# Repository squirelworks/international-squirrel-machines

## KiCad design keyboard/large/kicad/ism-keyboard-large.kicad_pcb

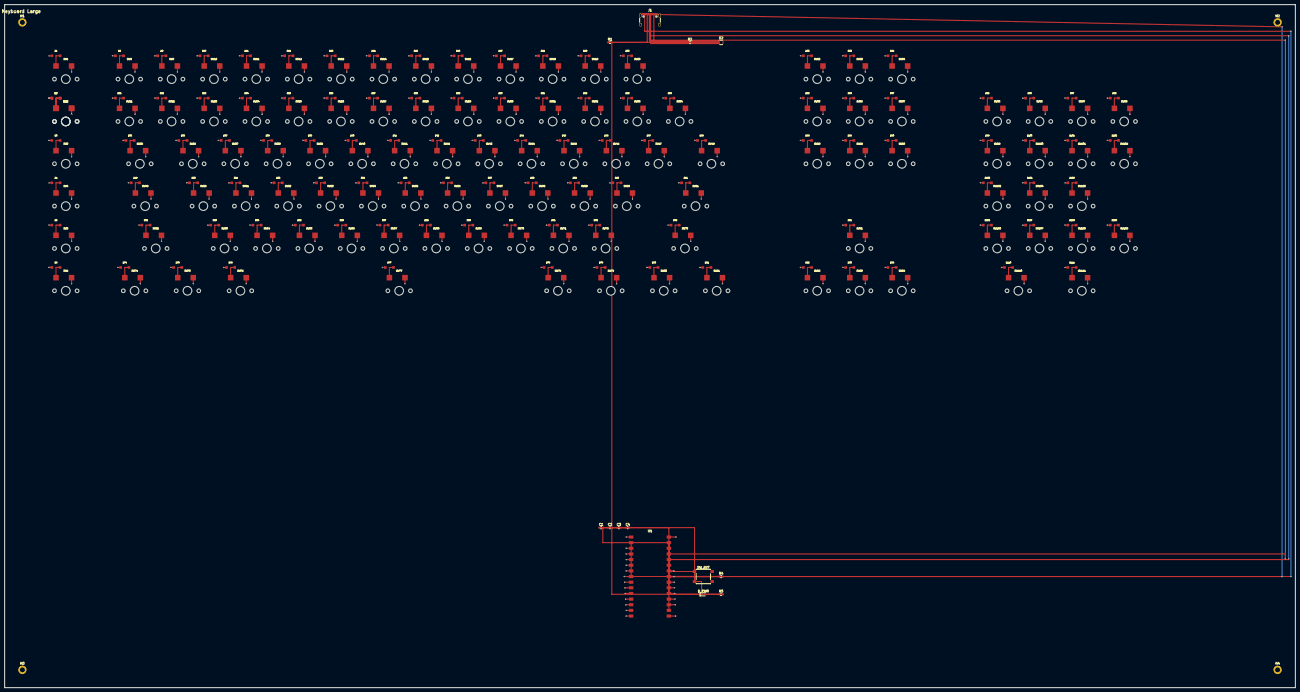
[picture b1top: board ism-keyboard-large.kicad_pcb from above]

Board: 4 copper layers, 580.8 x 307.4 mm, 239 parts (0 on the bottom side), 143 nets.

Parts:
C1, C2, C3, C4: 100nF; C_0603_1608Metric
D1, D2, D3, D4, D5, D6, D7, D8, D9, D10, D11, D12, D13, D14, D15, D16, D17, D18, D19, D20, D21, D22, D23, D24, D25, D26, D27, D28, D29, D30, D31, D32, D33, D34, D35, D36, D37, D38, D39, D40, D41, D42, D43, D44, D45, D46, D47, D48, D49, D50, D51, D52, D53, D54, D55, D56, D57, D58, D59, D60, D61, D62, D63, D64, D65, D66, D67, D68, D69, D70, D71, D72, D73, D74, D75, D76, D77, D78, D79, D80, D81, D82, D83, D84, D85, D86, D87, D88, D89, D90, D91, D92, D93, D94, D95, D96, D97, D98, D99, D100, D101, D102, D103, D104, D105, D106, D107, D108, D109, D110, D111: 1N4148W; D_SOD123_nocrt
D_PWR: LED; LED_0603_1608Metric
H1, H2, H3, H4: M2; MountingHole_2.2mm_M2_DIN965_Pad
J1: USB_C; USB_C_Receptacle_GCT_USB4105-xx-A_16P_TopMnt_Horizontal
R1, R2: 5.1k; R_0603_1608Metric
R4: 10k; R_0603_1608Metric
R5: 1k; R_0603_1608Metric
SW1: M1; SW_MX_Hotswap
SW2: M2; SW_MX_Hotswap
SW3: M3; SW_MX_Hotswap
SW4: M4; SW_MX_Hotswap
SW5: M5; SW_MX_Hotswap
SW6: M6; SW_MX_Hotswap
SW7: M7; SW_MX_Hotswap
SW8: ESC; SW_MX_Hotswap
SW9: F1; SW_MX_Hotswap
SW10: F2; SW_MX_Hotswap
SW11: F3; SW_MX_Hotswap
SW12: F4; SW_MX_Hotswap
SW13: F5; SW_MX_Hotswap
SW14: F6; SW_MX_Hotswap
SW15: F7; SW_MX_Hotswap
SW16: F8; SW_MX_Hotswap
SW17: F9; SW_MX_Hotswap
SW18: F10; SW_MX_Hotswap
SW19: F11; SW_MX_Hotswap
SW20: F12; SW_MX_Hotswap
SW21: GRV; SW_MX_Hotswap
SW22: 1; SW_MX_Hotswap
SW23: 2; SW_MX_Hotswap
SW24: 3; SW_MX_Hotswap
SW25: 4; SW_MX_Hotswap
SW26: 5; SW_MX_Hotswap
SW27: 6; SW_MX_Hotswap
SW28: 7; SW_MX_Hotswap
SW29: 8; SW_MX_Hotswap
SW30: 9; SW_MX_Hotswap
SW31: 0; SW_MX_Hotswap
SW32: MIN; SW_MX_Hotswap
SW33: EQL; SW_MX_Hotswap
SW34: BSPC; SW_MX_Hotswap
SW35: TAB; SW_MX_Hotswap
SW36: Q; SW_MX_Hotswap
SW37: W; SW_MX_Hotswap
SW38: E; SW_MX_Hotswap
SW39: R; SW_MX_Hotswap
SW40: T; SW_MX_Hotswap
SW41: Y; SW_MX_Hotswap
SW42: U; SW_MX_Hotswap
SW43: I; SW_MX_Hotswap
SW44: O; SW_MX_Hotswap
SW45: P; SW_MX_Hotswap
SW46: LBRC; SW_MX_Hotswap
SW47: RBRC; SW_MX_Hotswap
SW48: BSLS; SW_MX_Hotswap
SW49: CAPS; SW_MX_Hotswap
SW50: A; SW_MX_Hotswap
SW51: S; SW_MX_Hotswap
SW52: D; SW_MX_Hotswap
SW53: F; SW_MX_Hotswap
SW54: G; SW_MX_Hotswap
SW55: H; SW_MX_Hotswap
SW56: J; SW_MX_Hotswap
SW57: K; SW_MX_Hotswap
SW58: L; SW_MX_Hotswap
SW59: SCLN; SW_MX_Hotswap
SW60: QUOT; SW_MX_Hotswap
SW61: ENT; SW_MX_Hotswap
SW62: LSFT; SW_MX_Hotswap
SW63: Z; SW_MX_Hotswap
SW64: X; SW_MX_Hotswap
SW65: C; SW_MX_Hotswap
SW66: V; SW_MX_Hotswap
SW67: B; SW_MX_Hotswap
SW68: N; SW_MX_Hotswap
SW69: M; SW_MX_Hotswap
SW70: COMM; SW_MX_Hotswap
SW71: DOT; SW_MX_Hotswap
SW72: SLSH; SW_MX_Hotswap
SW73: RSFT; SW_MX_Hotswap
SW74: LCTL; SW_MX_Hotswap
SW75: LGUI; SW_MX_Hotswap
SW76: LALT; SW_MX_Hotswap
SW77: SPC; SW_MX_Hotswap
SW78: RALT; SW_MX_Hotswap
SW79: RGUI; SW_MX_Hotswap
SW80: MENU; SW_MX_Hotswap
SW81: RCTL; SW_MX_Hotswap
SW82: PRSC; SW_MX_Hotswap
SW83: SLCK; SW_MX_Hotswap
SW84: PAUSE; SW_MX_Hotswap
SW85: INS; SW_MX_Hotswap
SW86: HOME; SW_MX_Hotswap
SW87: PGUP; SW_MX_Hotswap
SW88: DEL; SW_MX_Hotswap
SW89: END; SW_MX_Hotswap
SW90: PGDN; SW_MX_Hotswap
SW91: UP; SW_MX_Hotswap
SW92: LEFT; SW_MX_Hotswap
SW93: DOWN; SW_MX_Hotswap
SW94: RIGHT; SW_MX_Hotswap
SW95: NUMLK; SW_MX_Hotswap
SW96: NPDIV; SW_MX_Hotswap
SW97: NPMUL; SW_MX_Hotswap
SW98: NPSUB; SW_MX_Hotswap
SW99: NP7; SW_MX_Hotswap
SW100: NP8; SW_MX_Hotswap
SW101: NP9; SW_MX_Hotswap
SW102: NPADD; SW_MX_Hotswap
SW103: NP4; SW_MX_Hotswap
SW104: NP5; SW_MX_Hotswap
SW105: NP6; SW_MX_Hotswap
SW106: NP1; SW_MX_Hotswap
SW107: NP2; SW_MX_Hotswap
SW108: NP3; SW_MX_Hotswap
SW109: NPENT; SW_MX_Hotswap
SW110: NP0; SW_MX_Hotswap
SW111: NPDOT; SW_MX_Hotswap
SW_RST: RESET; SW_SPST_PTS645
U1: RP2040_MOD; ISM_RP2040_Module
U2: USBLC6-2SC6; SOT-666

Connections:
+3V3: C1.1, C2.1, C3.1, C4.1, R4.2, R5.1, U1.14
+5V: J1.A4, J1.A9, J1.B4, J1.B9, U1.15, U2.5
CC1: J1.A5, R1.1
CC2: J1.B5, R2.1
COL0: D8.1, D21.1, D35.1, D49.1, D62.1, D74.1, D95.1, U1.7
COL1: D9.1, D22.1, D36.1, D50.1, D63.1, D75.1, D96.1, U1.8
COL2: D10.1, D23.1, D37.1, D51.1, D64.1, D76.1, D97.1, U1.9
COL3: D11.1, D24.1, D38.1, D52.1, D65.1, D77.1, D98.1, U1.10
COL4: D12.1, D25.1, D39.1, D53.1, D66.1, D78.1, D99.1, U1.11
COL5: D13.1, D26.1, D40.1, D54.1, D67.1, D79.1, D100.1, U1.12
COL6: D14.1, D27.1, D41.1, D55.1, D68.1, D80.1, D101.1, U1.13
COL7: D15.1, D28.1, D42.1, D56.1, D69.1, D81.1, D102.1, U1.19
COL8: D16.1, D29.1, D43.1, D57.1, D70.1, D84.1, D103.1, U1.20
COL9: D17.1, D30.1, D44.1, D58.1, D71.1, D92.1, D104.1, U1.21
COL10: D18.1, D31.1, D45.1, D59.1, D72.1, D93.1, D105.1, U1.22
COL11: D19.1, D32.1, D46.1, D60.1, D73.1, D94.1, D106.1, U1.23
COL12: D20.1, D33.1, D47.1, D61.1, D89.1, D107.1, D110.1, U1.24
COL13: D34.1, D48.1, D82.1, D86.1, D90.1, D108.1, D111.1, U1.25
COL14: D83.1, D85.1, D87.1, D88.1, D91.1, D109.1, U1.28
COL15: D1.1, D2.1, D3.1, D4.1, D5.1, D6.1, D7.1, U1.30
GND: C1.2, C2.2, C3.2, C4.2, D_PWR.1, J1.A1, J1.A8, J1.A12, J1.B1, J1.B8, J1.B12, J1.S1, R1.2, R2.2, SW_RST.2, U1.1, U1.26, U2.2
LED_A: D_PWR.2, R5.2
NET_SW1: D1.2, SW1.2
NET_SW2: D2.2, SW2.2
NET_SW3: D3.2, SW3.2
NET_SW4: D4.2, SW4.2
NET_SW5: D5.2, SW5.2
NET_SW6: D6.2, SW6.2
NET_SW7: D7.2, SW7.2
NET_SW8: D8.2, SW8.2
NET_SW9: D9.2, SW9.2
NET_SW10: D10.2, SW10.2
NET_SW11: D11.2, SW11.2
NET_SW12: D12.2, SW12.2
NET_SW13: D13.2, SW13.2
NET_SW14: D14.2, SW14.2
NET_SW15: D15.2, SW15.2
NET_SW16: D16.2, SW16.2
NET_SW17: D17.2, SW17.2
NET_SW18: D18.2, SW18.2
NET_SW19: D19.2, SW19.2
NET_SW20: D20.2, SW20.2
NET_SW21: D21.2, SW21.2
NET_SW22: D22.2, SW22.2
NET_SW23: D23.2, SW23.2
NET_SW24: D24.2, SW24.2
NET_SW25: D25.2, SW25.2
NET_SW26: D26.2, SW26.2
NET_SW27: D27.2, SW27.2
NET_SW28: D28.2, SW28.2
NET_SW29: D29.2, SW29.2
NET_SW30: D30.2, SW30.2
NET_SW31: D31.2, SW31.2
NET_SW32: D32.2, SW32.2
NET_SW33: D33.2, SW33.2
NET_SW34: D34.2, SW34.2
NET_SW35: D35.2, SW35.2
NET_SW36: D36.2, SW36.2
NET_SW37: D37.2, SW37.2
NET_SW38: D38.2, SW38.2
NET_SW39: D39.2, SW39.2
NET_SW40: D40.2, SW40.2
NET_SW41: D41.2, SW41.2
NET_SW42: D42.2, SW42.2
NET_SW43: D43.2, SW43.2
NET_SW44: D44.2, SW44.2
NET_SW45: D45.2, SW45.2
NET_SW46: D46.2, SW46.2
NET_SW47: D47.2, SW47.2
NET_SW48: D48.2, SW48.2
NET_SW49: D49.2, SW49.2
NET_SW50: D50.2, SW50.2
NET_SW51: D51.2, SW51.2
NET_SW52: D52.2, SW52.2
NET_SW53: D53.2, SW53.2
NET_SW54: D54.2, SW54.2
NET_SW55: D55.2, SW55.2
NET_SW56: D56.2, SW56.2
NET_SW57: D57.2, SW57.2
NET_SW58: D58.2, SW58.2
NET_SW59: D59.2, SW59.2
NET_SW60: D60.2, SW60.2
NET_SW61: D61.2, SW61.2
NET_SW62: D62.2, SW62.2
NET_SW63: D63.2, SW63.2
NET_SW64: D64.2, SW64.2
NET_SW65: D65.2, SW65.2
NET_SW66: D66.2, SW66.2
NET_SW67: D67.2, SW67.2
NET_SW68: D68.2, SW68.2
NET_SW69: D69.2, SW69.2
NET_SW70: D70.2, SW70.2
NET_SW71: D71.2, SW71.2
NET_SW72: D72.2, SW72.2
NET_SW73: D73.2, SW73.2
NET_SW74: D74.2, SW74.2
NET_SW75: D75.2, SW75.2
NET_SW76: D76.2, SW76.2
NET_SW77: D77.2, SW77.2
NET_SW78: D78.2, SW78.2
NET_SW79: D79.2, SW79.2
NET_SW80: D80.2, SW80.2
NET_SW81: D81.2, SW81.2
NET_SW82: D82.2, SW82.2
NET_SW83: D83.2, SW83.2
NET_SW84: D84.2, SW84.2
NET_SW85: D85.2, SW85.2
NET_SW86: D86.2, SW86.2
NET_SW87: D87.2, SW87.2
NET_SW88: D88.2, SW88.2
NET_SW89: D89.2, SW89.2
NET_SW90: D90.2, SW90.2
NET_SW91: D91.2, SW91.2
NET_SW92: D92.2, SW92.2
NET_SW93: D93.2, SW93.2
NET_SW94: D94.2, SW94.2
NET_SW95: D95.2, SW95.2
NET_SW96: D96.2, SW96.2
NET_SW97: D97.2, SW97.2
NET_SW98: D98.2, SW98.2
NET_SW99: D99.2, SW99.2
NET_SW100: D100.2, SW100.2
NET_SW101: D101.2, SW101.2
NET_SW102: D102.2, SW102.2
NET_SW103: D103.2, SW103.2
NET_SW104: D104.2, SW104.2
NET_SW105: D105.2, SW105.2
NET_SW106: D106.2, SW106.2
NET_SW107: D107.2, SW107.2
NET_SW108: D108.2, SW108.2
NET_SW109: D109.2, SW109.2
NET_SW110: D110.2, SW110.2
NET_SW111: D111.2, SW111.2
ROW0: SW1.1, SW8.1, SW9.1, SW10.1, SW11.1, SW12.1, SW13.1, SW14.1, SW15.1, SW16.1, SW17.1, SW18.1, SW19.1, SW20.1, SW82.1, SW83.1, U1.2
ROW1: SW2.1, SW21.1, SW22.1, SW23.1, SW24.1, SW25.1, SW26.1, SW27.1, SW28.1, SW29.1, SW30.1, SW31.1, SW32.1, SW33.1, SW34.1, SW85.1, U1.3
ROW2: SW3.1, SW35.1, SW36.1, SW37.1, SW38.1, SW39.1, SW40.1, SW41.1, SW42.1, SW43.1, SW44.1, SW45.1, SW46.1, SW47.1, SW48.1, SW88.1, U1.4
ROW3: SW4.1, SW49.1, SW50.1, SW51.1, SW52.1, SW53.1, SW54.1, SW55.1, SW56.1, SW57.1, SW58.1, SW59.1, SW60.1, SW61.1, SW86.1, SW87.1, U1.5
ROW4: SW5.1, SW62.1, SW63.1, SW64.1, SW65.1, SW66.1, SW67.1, SW68.1, SW69.1, SW70.1, SW71.1, SW72.1, SW73.1, SW89.1, SW90.1, SW91.1, U1.6
ROW5: SW6.1, SW74.1, SW75.1, SW76.1, SW77.1, SW78.1, SW79.1, SW80.1, SW81.1, SW84.1, SW92.1, SW93.1, SW94.1, SW110.1, SW111.1, U1.27
ROW6: SW7.1, SW95.1, SW96.1, SW97.1, SW98.1, SW99.1, SW100.1, SW101.1, SW102.1, SW103.1, SW104.1, SW105.1, SW106.1, SW107.1, SW108.1, SW109.1, U1.29
RUN: R4.1, SW_RST.1, U1.18
USB_DM: J1.A7, J1.B7, U1.16, U2.3, U2.4
USB_DP: J1.A6, J1.B6, U1.17, U2.1, U2.6

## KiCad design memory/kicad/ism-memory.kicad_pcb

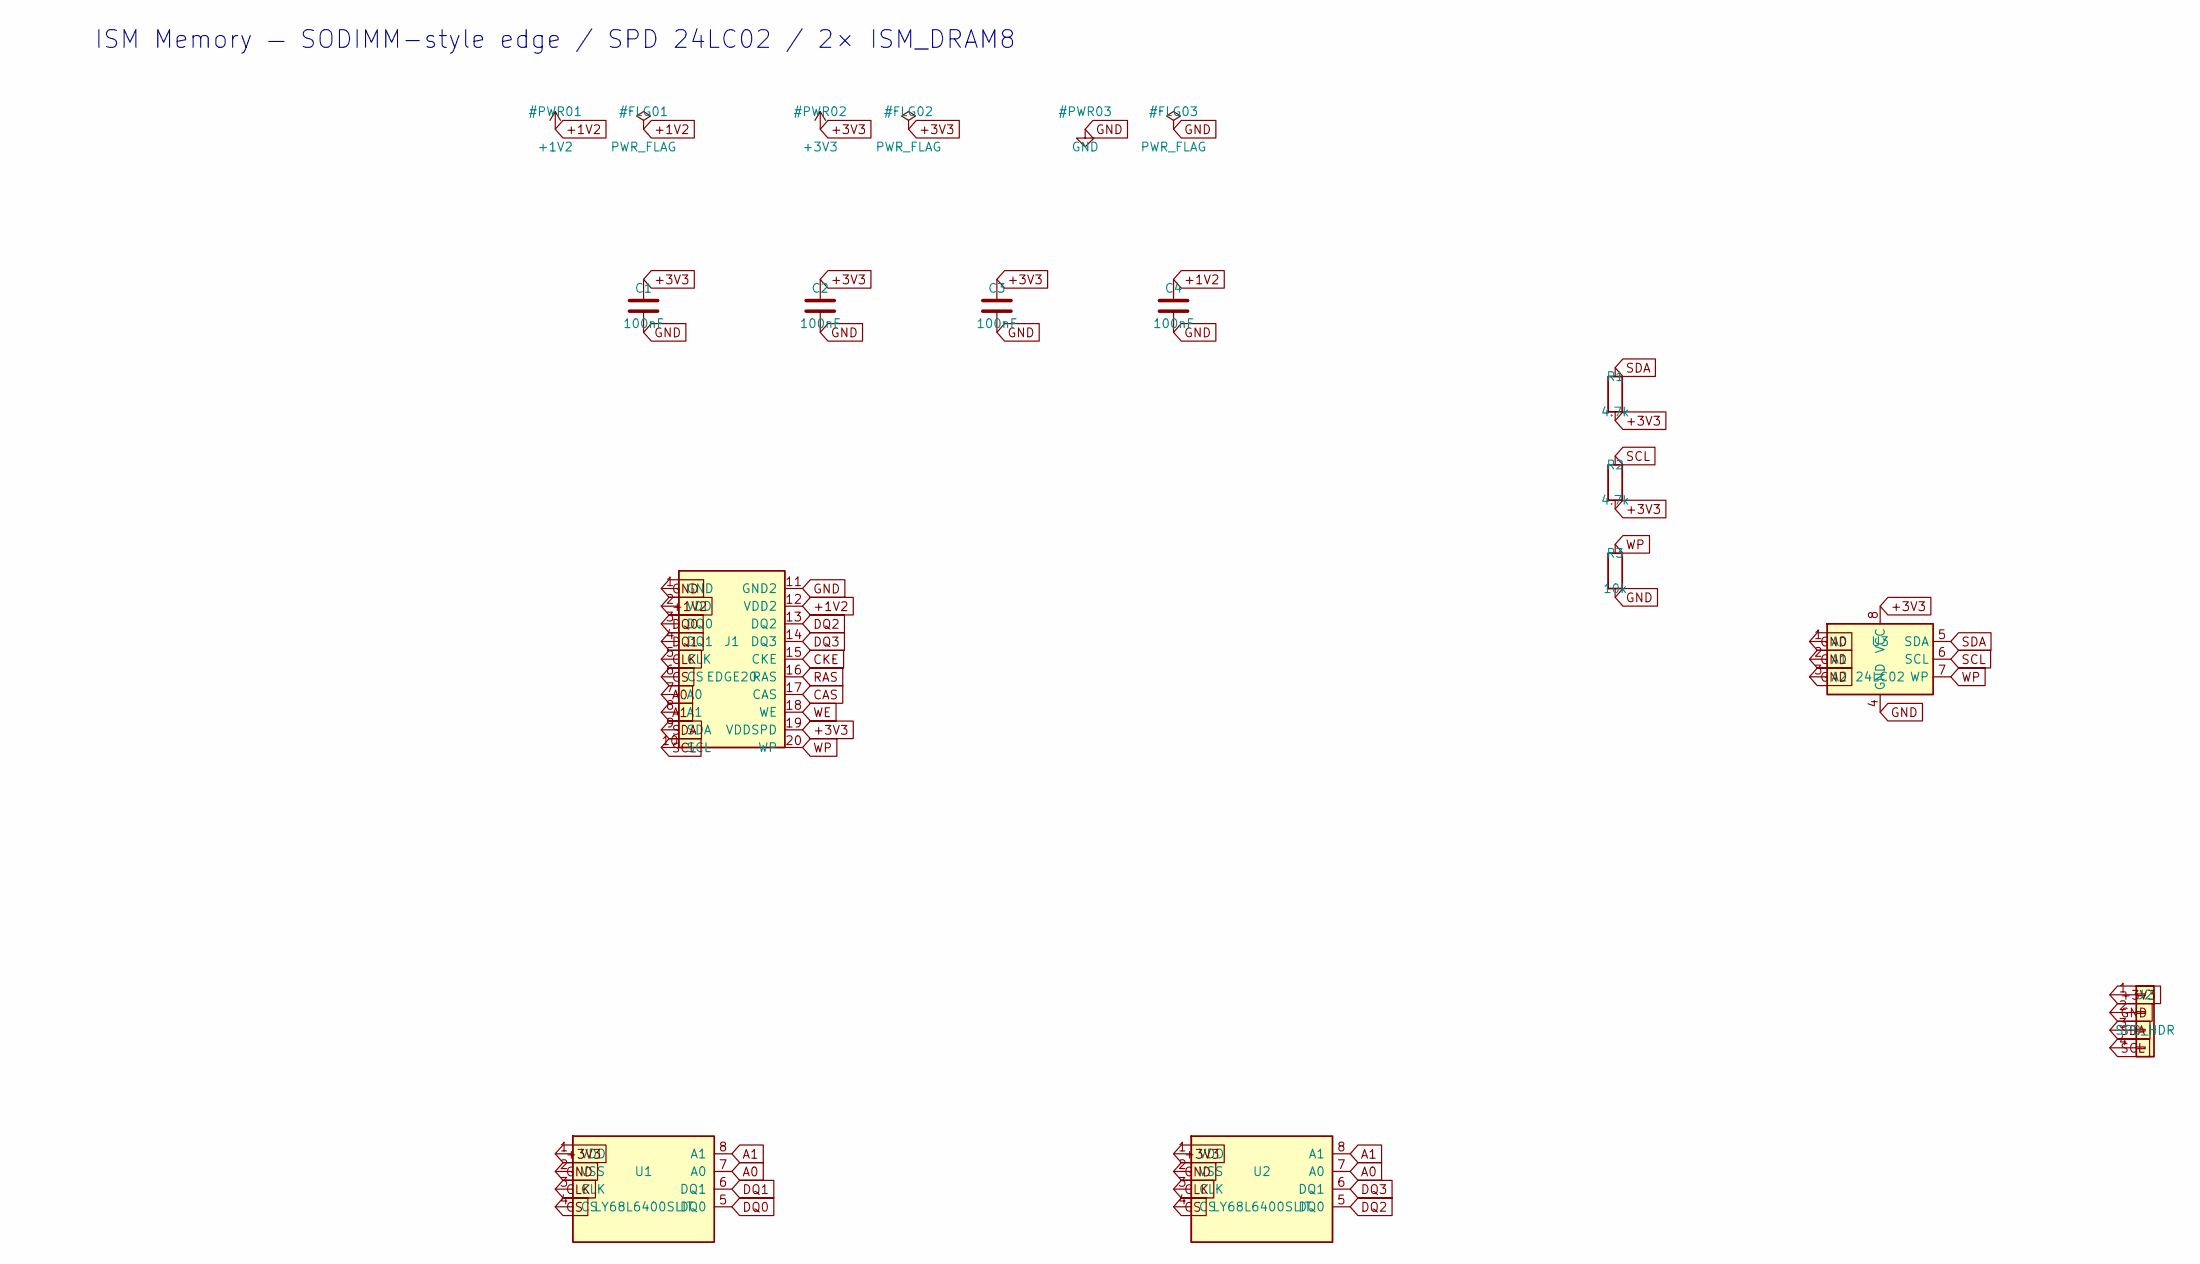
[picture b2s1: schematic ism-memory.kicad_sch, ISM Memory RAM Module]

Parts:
C1, C2, C3, C4: 100nF; C_0603_1608Metric; LCSC C14663
J1: EDGE20; ISM_SO_DIMM_Edge20
J2: SPD_HDR; PinHeader_1x04_P2.54mm_Vertical
R1, R2: 4.7k; R_0603_1608Metric; LCSC C23141
R3: 10k; R_0603_1608Metric; LCSC C25804
U1, U2: LY68L6400SLIT; SOIC-8_3.9x4.9mm_P1.27mm; MPN LY68L6400SLIT; LCSC C261881
U3: 24LC02; SOIC-8_3.9x4.9mm_P1.27mm; MPN 24LC02B; LCSC C7500

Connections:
+1V2: C4.1, J1.2 (VDD), J1.12 (VDD2)
+3V3: C1.1, C2.1, C3.1, J1.19 (VDDSPD), J2.1, R1.2, R2.2, U1.1 (VDD), U2.1 (VDD), U3.8 (VCC)
A0: J1.7 (A0), U1.7 (A0), U2.7 (A0)
A1: J1.8 (A1), U1.8 (A1), U2.8 (A1)
CAS: J1.17 (CAS)
CKE: J1.15 (CKE)
CLK: J1.5 (CLK), U1.3 (CLK), U2.3 (CLK)
CS: J1.6 (CS), U1.4 (CS), U2.4 (CS)
DQ0: J1.3 (DQ0), U1.5 (DQ0)
DQ1: J1.4 (DQ1), U1.6 (DQ1)
DQ2: J1.13 (DQ2), U2.5 (DQ0)
DQ3: J1.14 (DQ3), U2.6 (DQ1)
GND: C1.2, C2.2, C3.2, C4.2, J1.1 (GND), J1.11 (GND2), J2.2, R3.2, U1.2 (VSS), U2.2 (VSS), U3.1 (A0), U3.2 (A1), U3.3 (A2), U3.4 (GND)
RAS: J1.16 (RAS)
SCL: J1.10 (SCL), J2.4, R2.1, U3.6 (SCL)
SDA: J1.9 (SDA), J2.3, R1.1, U3.5 (SDA)
WE: J1.18 (WE)
WP: J1.20 (WP), R3.1, U3.7 (WP)

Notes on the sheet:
ISM Memory — SODIMM-style edge / SPD 24LC02 / 2× ISM_DRAM8

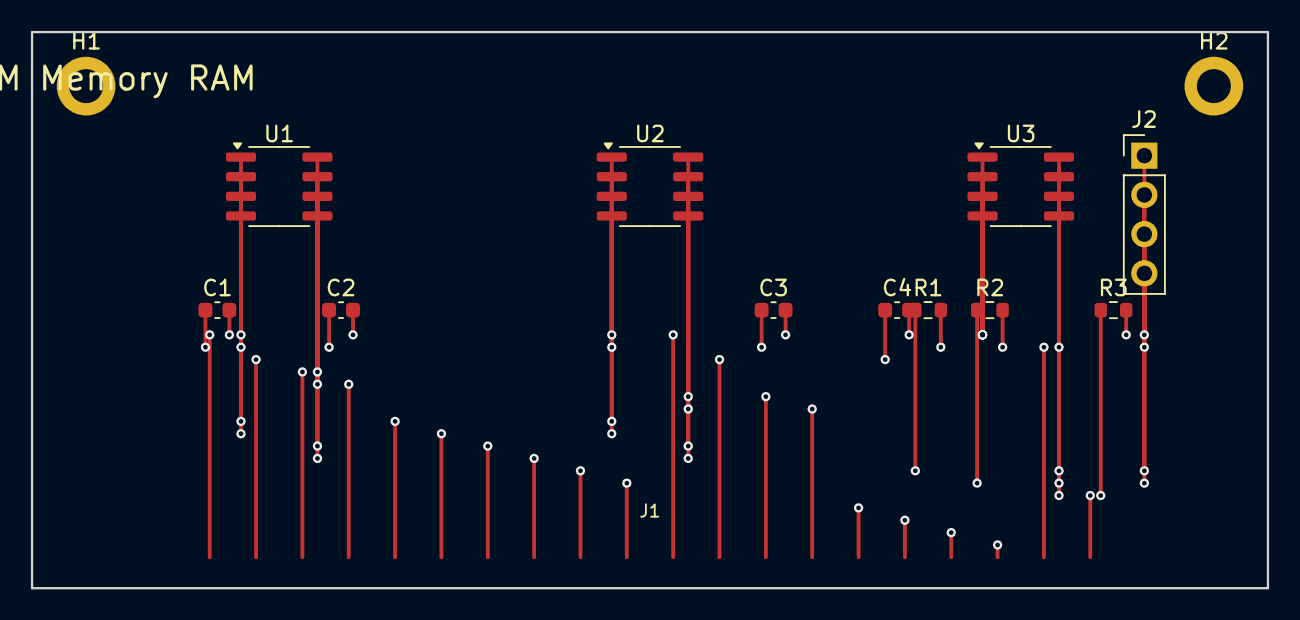
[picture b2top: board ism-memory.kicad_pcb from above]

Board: 4 copper layers, 80.0 x 36.0 mm, 14 parts (0 on the bottom side), 14 nets.

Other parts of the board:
H1, H2: M2; MountingHole_2.2mm_M2_DIN965_Pad

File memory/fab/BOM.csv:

Designator,Value,Footprint,Quantity,Manufacturer,MPN,LCSC,Notes
"U1,U2",LY68L6400SLIT,SOIC-8_3.9x4.9mm,2,Lyontek,LY68L6400SLIT,C261881,Default SMT pop — 64 Mbit SPI/QPI PSRAM. Optional alt land: ISM:ISM_DRAM_SOIC
U3,24LC02,SOIC-8,1,Microchip,24LC02B,C7500,SPD EEPROM
J1,EDGE20,ISM_SO_DIMM_Edge20,1,ISM,ISM-EDGE20,,No LCSC — edge fingers (PCB feature)
J2,1x04,PinHeader 2.54,1,,HDR-1x4,C124423,SPD test header
"R1,R2",4.7k,0603,2,,4.7k,C23141,I2C pull-up
R3,10k,0603,1,,10k,C25804,WP pull-down
C1-C4,100nF,0603,4,,100nF,C14663,
"H1,H2",M2,MountingHole,2,,,,No LCSC — mechanical NPTH

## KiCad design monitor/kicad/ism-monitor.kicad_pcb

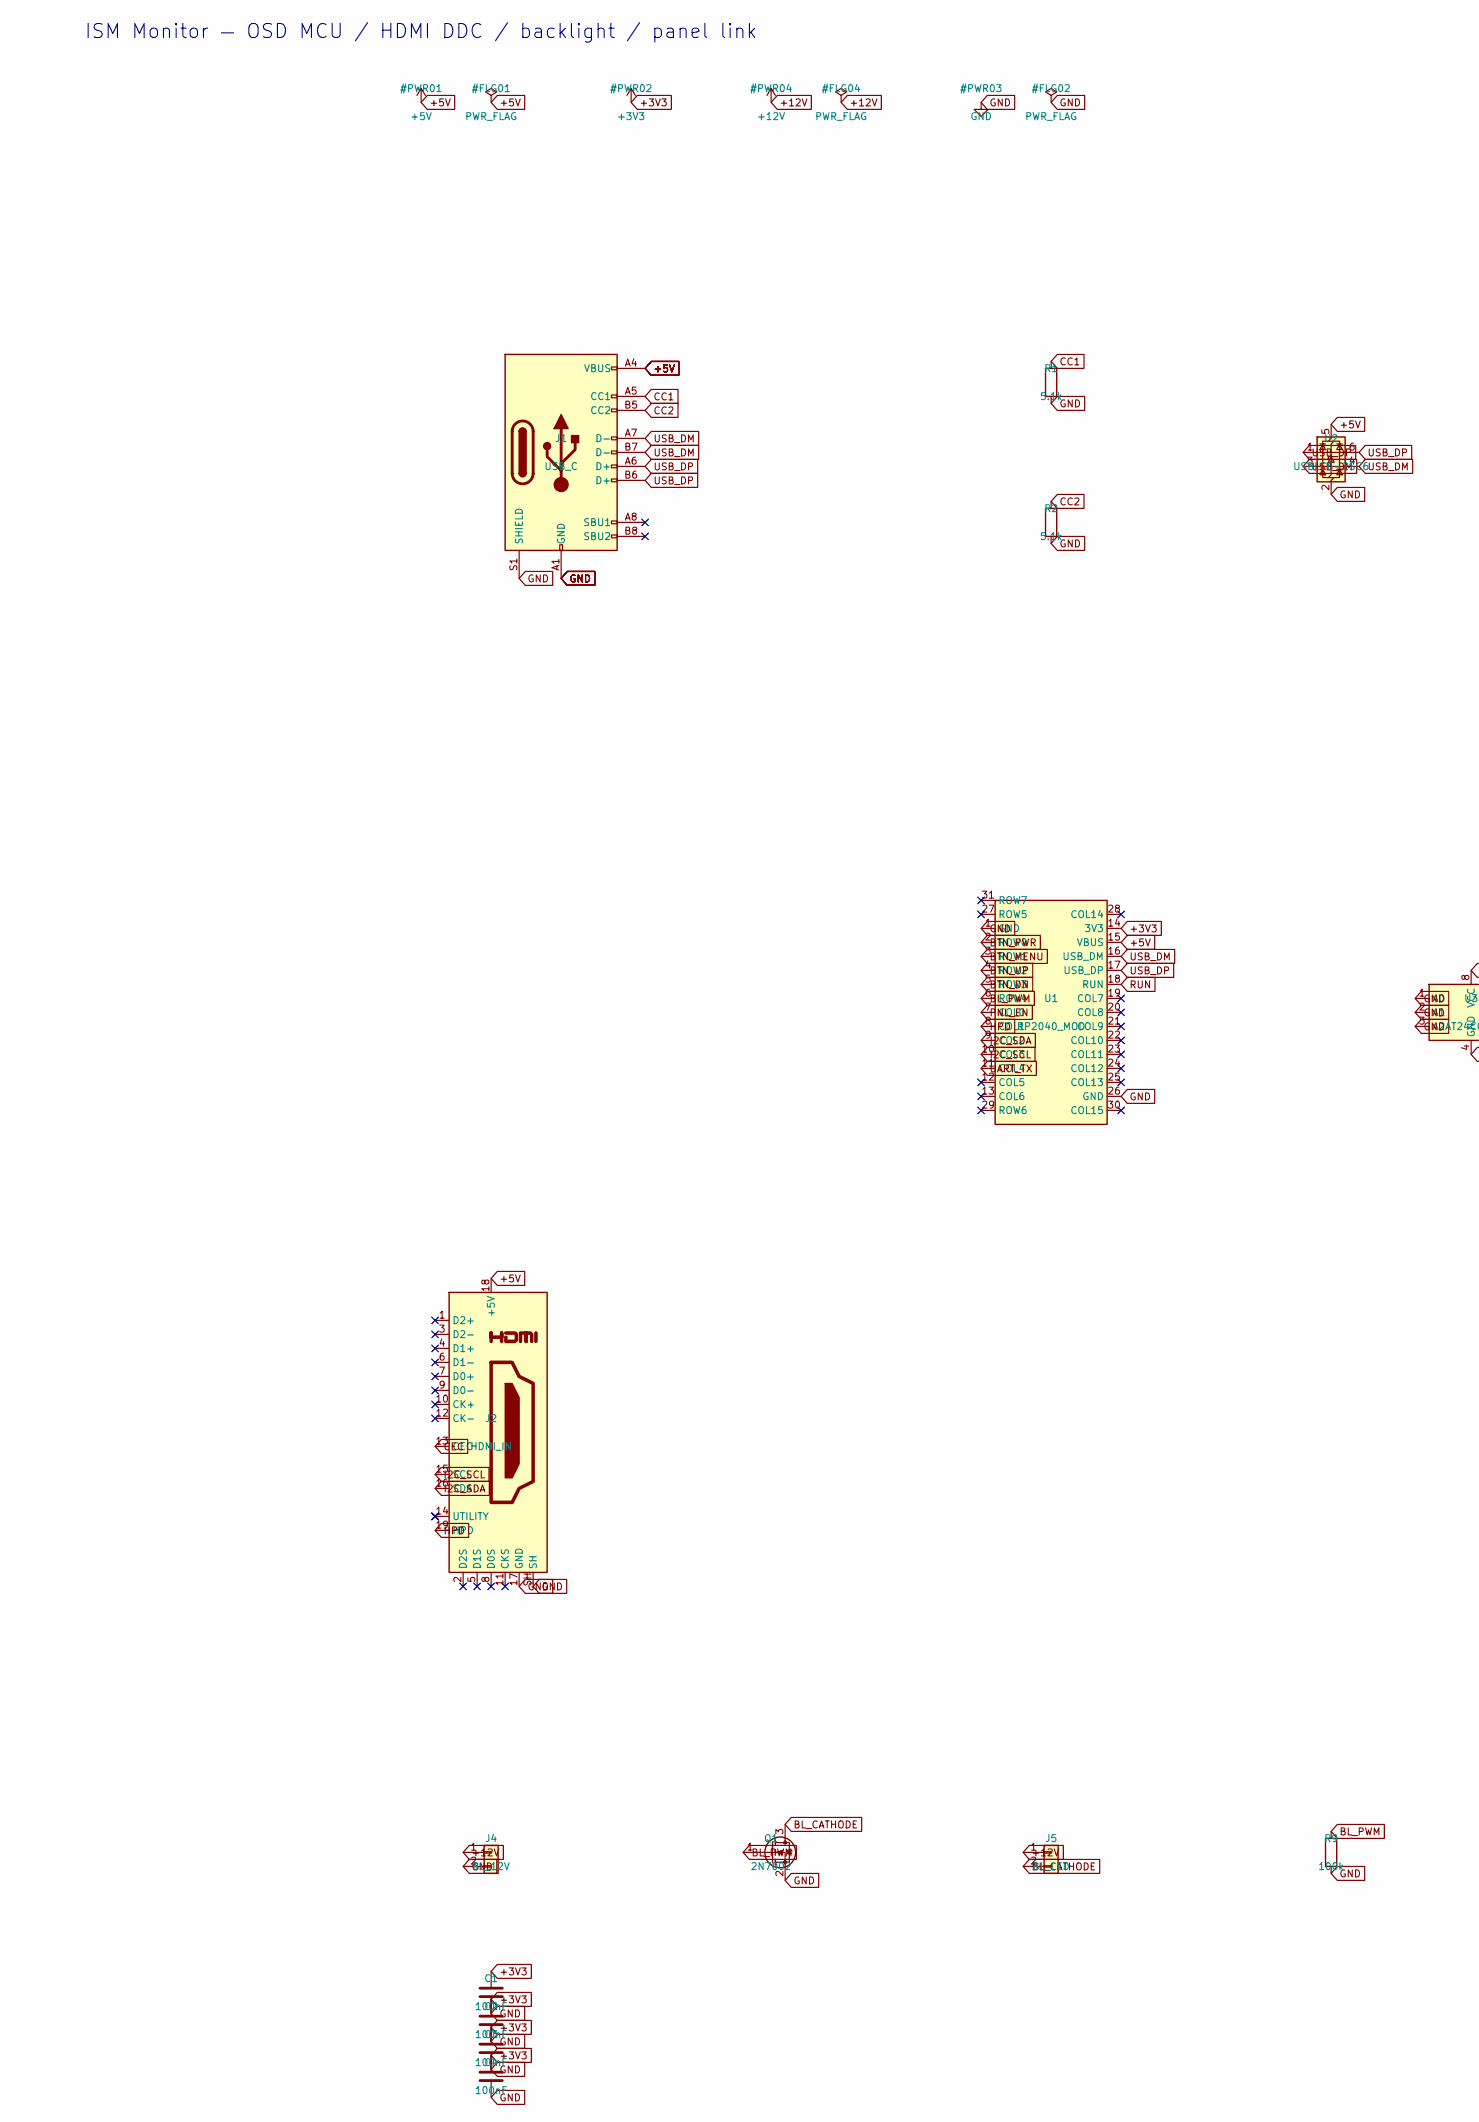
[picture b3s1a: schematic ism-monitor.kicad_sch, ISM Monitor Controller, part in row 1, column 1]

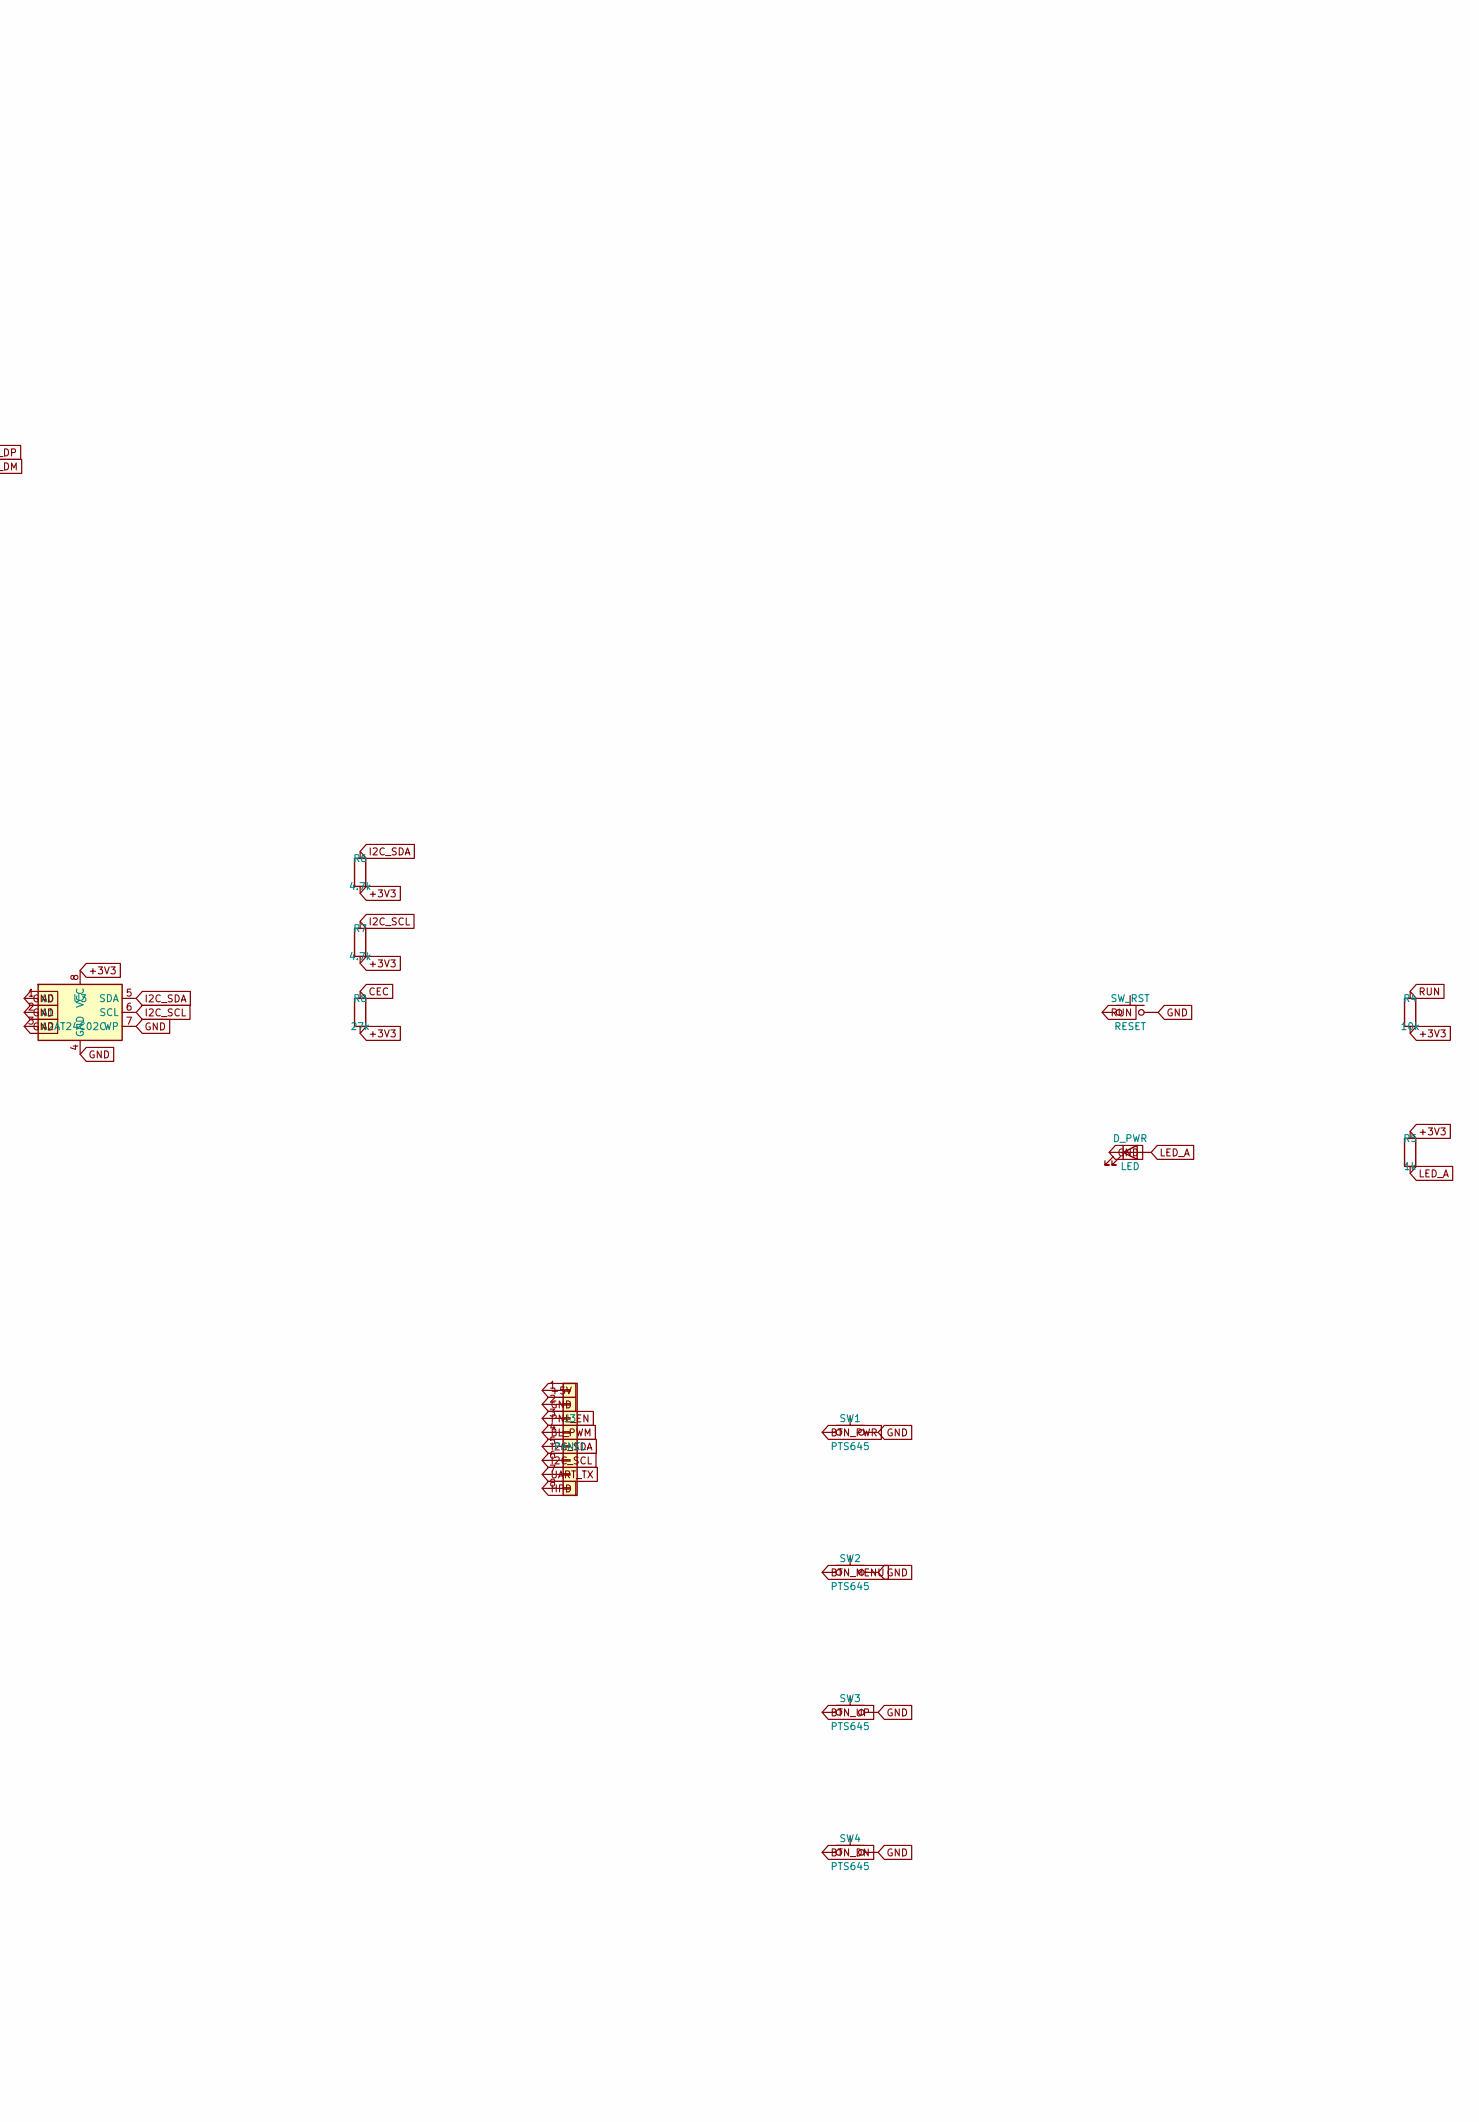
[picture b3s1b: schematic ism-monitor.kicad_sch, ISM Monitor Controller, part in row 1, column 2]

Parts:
C1, C2, C3, C4: 100nF; C_0603_1608Metric; LCSC C14663
D_PWR: LED; LED_0603_1608Metric; LCSC C2286
J1: USB_C; USB_C_Receptacle_GCT_USB4105-xx-A_16P_TopMnt_Horizontal; LCSC C165948
J2: HDMI_IN; HDMI_A_Amphenol_10029449-x01xLF_Horizontal; LCSC C132555
J3: PANEL; PinHeader_1x08_P2.54mm_Vertical
J4: BL_12V; PinHeader_1x02_P2.54mm_Vertical
J5: BL_LED; PinHeader_1x02_P2.54mm_Vertical
Q1: 2N7002; SOT-23; MPN 2N7002; LCSC C8545
R1, R2: 5.1k; R_0603_1608Metric; LCSC C23244
R4: 10k; R_0603_1608Metric; LCSC C25804
R5: 1k; R_0603_1608Metric; LCSC C21190
R6, R7: 4.7k; R_0603_1608Metric; LCSC C23141
R8: 27k; R_0603_1608Metric; LCSC C23286
R9: 100k; R_0603_1608Metric; LCSC C25803
SW1, SW2, SW3, SW4: PTS645; SW_SPST_PTS645; LCSC C318884
SW_RST: RESET; SW_SPST_PTS645; LCSC C318884
U1: RP2040_MOD; ISM_RP2040_Module; MPN ISM-RP2040-MOD
U2: USBLC6-2SC6; SOT-666; LCSC C7519
U3: AT24C02C; SOIC-8_3.9x4.9mm_P1.27mm; MPN AT24C02C-SSHM-T; LCSC C6203

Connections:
+3V3: C1.1, C2.1, C3.1, C4.1, R4.2, R5.1, R6.2, R7.2, R8.2, U1.14 (3V3), U3.8 (VCC)
+5V: J1.A4 (VBUS), J1.A9 (VBUS), J1.B4 (VBUS), J1.B9 (VBUS), J2.18 (+5V), J3.1, U1.15 (VBUS), U2.5 (VBUS)
+12V: J4.1, J5.1
BL_CATHODE: J5.2, Q1.3 (D)
BL_PWM: J3.4, Q1.1 (G), R9.1, U1.6 (ROW4)
BTN_DN: SW4.1, U1.5 (ROW3)
BTN_MENU: SW2.1, U1.3 (ROW1)
BTN_PWR: SW1.1, U1.2 (ROW0)
BTN_UP: SW3.1, U1.4 (ROW2)
CC1: J1.A5 (CC1), R1.1
CC2: J1.B5 (CC2), R2.1
CEC: J2.13 (CEC), R8.1
GND: C1.2, C2.2, C3.2, C4.2, D_PWR.1 (K), J1.A1 (GND), J1.A8 (SBU1), J1.A12 (GND), J1.B1 (GND), J1.B8 (SBU2), J1.B12 (GND), J1.S1 (SHIELD), J2.17 (GND), J2.SH, J3.2, J4.2, Q1.2 (S), R1.2, R2.2, R9.2, SW1.2, SW2.2, SW3.2, SW4.2, SW_RST.2, U1.1 (GND), U1.26 (GND), U2.2 (GND), U3.1 (A0), U3.2 (A1), U3.3 (A2), U3.4 (GND), U3.7 (WP)
HPD: J2.19 (HPD), J3.8, U1.8 (COL1)
I2C_SCL: J2.15 (SCL), J3.6, R7.1, U1.10 (COL3), U3.6 (SCL)
I2C_SDA: J2.16 (SDA), J3.5, R6.1, U1.9 (COL2), U3.5 (SDA)
LED_A: D_PWR.2 (A), R5.2
PNL_EN: J3.3, U1.7 (COL0)
RUN: R4.1, SW_RST.1, U1.18 (RUN)
UART_TX: J3.7, U1.11 (COL4)
USB_DM: J1.A7 (D-), J1.B7 (D-), U1.16 (USB_DM), U2.3 (I/O2), U2.4 (I/O2)
USB_DP: J1.A6 (D+), J1.B6 (D+), U1.17 (USB_DP), U2.1 (I/O1), U2.6 (I/O1)

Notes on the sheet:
ISM Monitor — OSD MCU / HDMI DDC / backlight / panel link

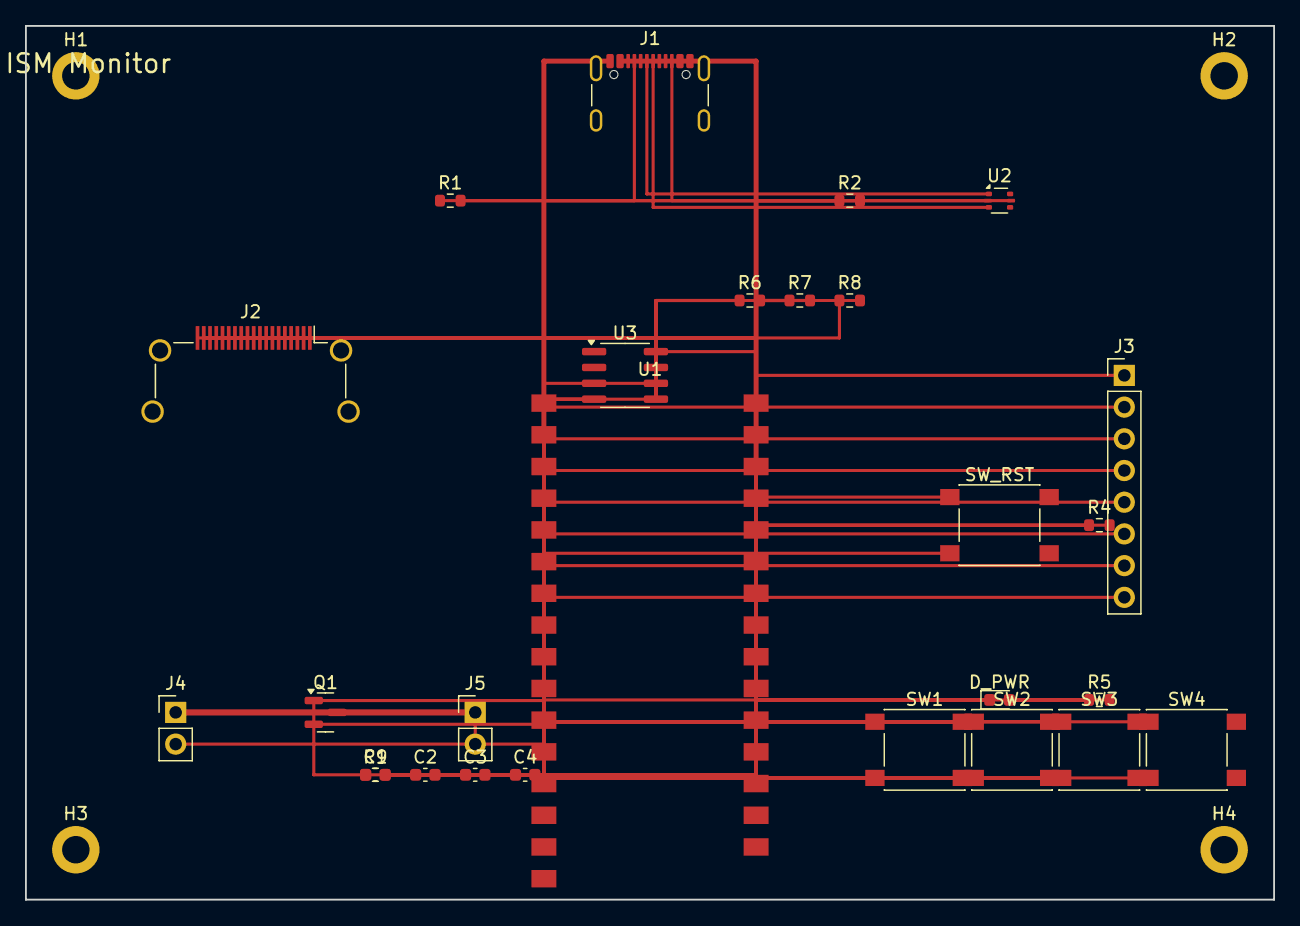
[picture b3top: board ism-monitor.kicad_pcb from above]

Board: 4 copper layers, 100.0 x 70.0 mm, 31 parts (0 on the bottom side), 22 nets.

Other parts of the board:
H1, H2, H3, H4: M2; MountingHole_2.2mm_M2_DIN965_Pad
